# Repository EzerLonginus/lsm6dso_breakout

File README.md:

# LSM6DS0 Breakout
Simple breakout for the LSM6DSO Accelerometer and Gyroscope.  

## Purpose
I wanted to isolate this sensor and test out a basic design functionality, before trying to incorporate it into other designs.  

## Scematic

## Layout

## To Do
* Post pictures of populated board
* Test functionality

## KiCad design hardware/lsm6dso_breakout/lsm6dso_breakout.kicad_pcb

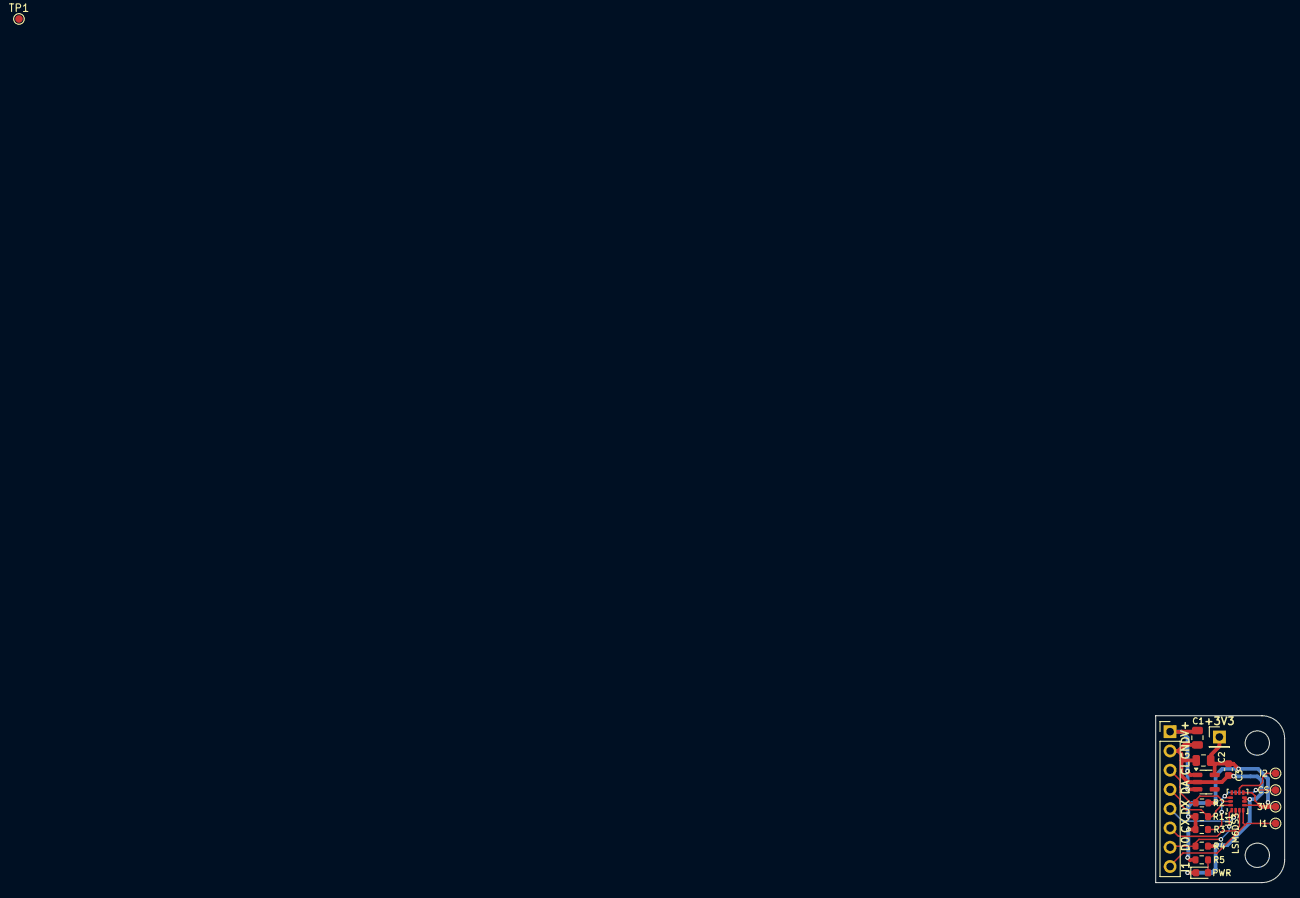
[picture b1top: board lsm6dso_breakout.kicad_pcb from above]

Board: 2 copper layers, 17.0 x 22.0 mm, 20 parts (0 on the bottom side), 12 nets.

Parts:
C1, C2: 10uF; C_0805_2012Metric
C3: 100nF; C_0603_1608Metric
D1: PWR; LED_0603_1608Metric
H1, H2: MountingHole; MountingHole_3.2mm_M3
J1: Conn_01x08_Pin; PinHeader_1x08_P2.54mm_Vertical
J2: +3V3; PinHeader_1x01_P2.54mm_Vertical
R1, R2: 4k7; R_0603_1608Metric
R3, R4, R5: 10k; R_0603_1608Metric
TP1: 3V3; TestPoint_Pad_D1.0mm
TP5: I1; TestPoint_Pad_D1.0mm
TP6: I2; TestPoint_Pad_D1.0mm
TP7: CS; TestPoint_Pad_D1.0mm
TP8: 3V; TestPoint_Pad_D1.0mm
U1: LSM6DS3; LGA-14_3x2.5mm_P0.5mm_LayoutBorder3x4y
U2: AP2112K-3.3; SOT-23-5

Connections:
+3V3: C2.1, C3.1, J2.1, R1.2, R2.1, R3.1, R5.1, TP8.1, U1.5 (VDDIO), U1.8 (VDD), U2.5 (VOUT)
/CS: R3.2, TP7.1, U1.12 (CS)
/INT1: J1.8, TP5.1, U1.4 (INT1)
/INT2: TP6.1, U1.9 (INT2)
/SCL: J1.3, R2.2, U1.13 (SCL)
/SCX: J1.6, U1.3 (SCX)
/SDA: J1.4, R1.1, U1.14 (SDA)
/SDO: J1.7, R4.1, U1.1 (SDO/SA0)
/SDX: J1.5, U1.2 (SDX)
GND: C1.2, C2.2, C3.2, D1.1 (K), J1.2, R4.2, U1.6 (GND), U1.7 (GND), U2.2 (GND)
unnamed: D1.2 (A), R5.2
VCC: C1.1, J1.1, U2.1 (VIN), U2.3 (EN)

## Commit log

2025-04-11 Initial Commit
